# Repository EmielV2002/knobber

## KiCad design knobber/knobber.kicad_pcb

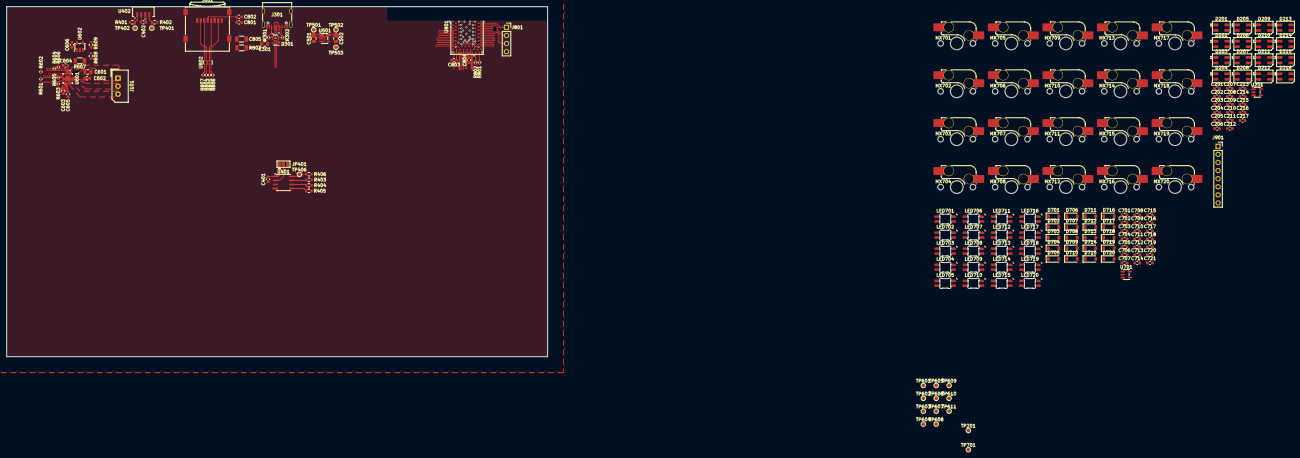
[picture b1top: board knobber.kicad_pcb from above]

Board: 4 copper layers, 189 parts (0 on the bottom side), 107 nets.

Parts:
C201, C202, C203, C204, C205, C206, C207, C208, C209, C210, C211, C212, C213, C214, C215, C216, C217, C401, C402, C701, C702, C703, C704, C705, C706, C707, C708, C709, C710, C711, C712, C713, C714, C715, C716, C717, C718, C719, C720, C721, C804: 0.1uF; C_0603_1608Metric
C301: 100nF; C_0805_2012Metric
C501, C502, C601: 10uF; C_0805_2012Metric
C602, C603, C604, C605, C606: 0.1nF; C_0603_1608Metric
C801, C802: 4.7uF; C_0603_1608Metric
C803: 10uF; C_0603_1608Metric
C805: 2.2uF; C_1206_3216Metric
D201, D202, D203, D204, D205, D206, D207, D208, D209, D210, D211, D212, D213, D214, D215, D216: SK6812MINI; LED_SK6812MINI_PLCC4_3.5x3.5mm_P1.75mm
D301: PRTR5V0U2X; SOT-143
D701, D702, D703, D704, D705, D706, D707, D708, D709, D710, D711, D712, D713, D714, D715, D716, D717, D718, D719, D720: 1N4148W; D_SOD-123
J101: BLDC; Molex_SPOX_5267-03A_1x03_P2.50mm_Vertical
J301: USB_C_Receptacle_USB2.0_16P; USB_C_Receptacle_G-Switch_GT-USB-7010ASV
J801: SWD; PinSocket_1x04_P2.54mm_Vertical
J802: Micro_SD_Card; microSD_HC_Wuerth_693072010801
J901: LCD; PinSocket_1x08_P2.54mm_Vertical
JP401: SolderJumper_3_Bridged12; SolderJumper-3_P1.3mm_Bridged12_Pad1.0x1.5mm
LED701, LED702, LED703, LED704, LED705, LED706, LED707, LED708, LED709, LED710, LED711, LED712, LED713, LED714, LED715, LED716, LED717, LED718, LED719, LED720: choc_SK6812MINI-E; LED_choc_6028R
MX701, MX702, MX703, MX704, MX705, MX706, MX707, MX708, MX709, MX710, MX711, MX712, MX713, MX714, MX715, MX716, MX717, MX718, MX719, MX720: MX_SW_HS; SW_MX_HS_CPG151101S11_1u
R301, R302: 5.1k; R_0402_1005Metric
R401, R402, R403, R404: 2.2k; R_0603_1608Metric
R405: 100k; R_0603_1608Metric
R406: 0; R_0603_1608Metric
R601, R602, R603, R604, R605, R606, R804, R805, R806, R807: 100k; R_0402_1005Metric
R607: 150m; R_1206_3216Metric
R608: 2k; R_0603_1608Metric
R609: 18k; R_0603_1608Metric
R801, R802: 27; R_0402_1005Metric
R803: 1M; R_1206_3216Metric
TP201, TP701: LED_DATA; TestPoint_Pad_D1.0mm
TP401: SDA; TestPoint_Pad_D1.0mm
TP402: SCL; TestPoint_Pad_D1.0mm
TP406: ENC__~{CS}; TestPoint_Pad_D1.0mm
TP501: 5V; TestPoint_Pad_D1.0mm
TP502: 3.3V; TestPoint_Pad_D1.0mm
TP503: GND; TestPoint_Pad_D1.0mm
TP601: MOT_UH; TestPoint_Pad_D1.0mm
TP602: MOT_UL; TestPoint_Pad_D1.0mm
TP603: MOT_VH; TestPoint_Pad_D1.0mm
TP604: MOT_VL; TestPoint_Pad_D1.0mm
TP605: MOT_WH; TestPoint_Pad_D1.0mm
TP606: MOT_WL; TestPoint_Pad_D1.0mm
TP607: Cur_sens; TestPoint_Pad_D1.0mm
TP608: MOT_DIAG; TestPoint_Pad_D1.0mm
TP609: MOT_U; TestPoint_Pad_D1.0mm
TP610: MOT_V; TestPoint_Pad_D1.0mm
TP611: MOT_W; TestPoint_Pad_D1.0mm
U201, U701: SN74LV1T34DBV; SOT-23-5
U401: MT6701CT; SO-8_3.9x4.9mm_P1.27mm
U402: VEML7700-TT
U501: AP2112K-3.3; SOT-23-5
U601: TMC6300-LA-T; QFN40P300X300X90-21N
U602: LMV321; SOT-23-5
U801: BMD-340-A-R; RIGADO_BMD-340-A-R
U802: ESD224DQA; Diodes_UDFN-10_1x2.5mm_P0.5mm

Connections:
3.3V: C402.1, C502.1, C603.1, C801.1, C802.1, C803.1, C804.1, J802.4 (VDD), J901.1, R401.2, R402.2, R403.2, R404.2, R804.2, R805.2, R806.2, R807.2, TP502.1, U402.2 (VDD), U501.5 (VOUT), U601.11 (VIO/~STDBY), U801.17 (VCC), U801.65 (VCCH)
5V: C201.1, C202.1, C203.1, C204.1, C205.1, C206.1, C207.1, C208.1, C209.1, C210.1, C211.1, C212.1, C213.1, C214.1, C215.1, C216.1, C217.1, C301.1, C401.1, C501.1, C601.1, C602.1, C604.1, C606.1, C701.1, C702.1, C703.1, C704.1, C705.1, C706.1, C707.1, C708.1, C709.1, C710.1, C711.1, C712.1, C713.1, C714.1, C715.1, C716.1, C717.1, C718.1, C719.1, C720.1, C721.1, D201.4 (VDD), D202.4 (VDD), D203.4 (VDD), D204.4 (VDD), D205.4 (VDD), D206.4 (VDD), D207.4 (VDD), D208.4 (VDD), D209.4 (VDD), D210.4 (VDD), D211.4 (VDD), D212.4 (VDD), D213.4 (VDD), D214.4 (VDD), D215.4 (VDD), D216.4 (VDD), D301.4 (VCC), J301.A4 (VBUS), J301.A9 (VBUS), J301.B4 (VBUS), J301.B9 (VBUS), JP401.1 (A), LED701.1 (VDD), LED702.1 (VDD), LED703.1 (VDD), LED704.1 (VDD), LED705.1 (VDD), LED706.1 (VDD), LED707.1 (VDD), LED708.1 (VDD), LED709.1 (VDD), LED710.1 (VDD), LED711.1 (VDD), LED712.1 (VDD), LED713.1 (VDD), LED714.1 (VDD), LED715.1 (VDD), LED716.1 (VDD), LED717.1 (VDD), LED718.1 (VDD), LED719.1 (VDD), LED720.1 (VDD), R406.2, TP501.1, U201.5 (VCC), U401.1 (VDD), U501.1 (VIN), U501.3 (EN), U601.2 (VCP), U601.18 (VS), U602.5 (V+), U701.5 (VCC), U801.66 (VBUS)
/MCU/SD_CLK: R805.1, U802.4
/MCU/SD_MISO: R806.1, U802.5
/MCU/SD_MOSI: R804.1, U802.2
/MCU/SD_~CS: R807.1, U802.1
/MCU/SW_CLK: J801.2, U801.43 (SWCLK)
/MCU/SW_DIO: J801.1, U801.44 (SWDIO)
/MCU/~RESET: J801.3, U801.39 (RESET)
/Motor driver/MOT_DIAG: TP608.1, U601.12 (DIAG)
/Motor driver/MOT_SENS: R609.1, U602.4
/Motor driver/MOT_U: J101.3, TP609.1, U601.15 (U)
/Motor driver/MOT_UH: R606.2, TP601.1, U601.3 (UH)
/Motor driver/MOT_UL: R605.2, TP602.1, U601.6 (UL)
/Motor driver/MOT_V: J101.2, TP610.1, U601.17 (V)
/Motor driver/MOT_VH: R604.2, TP603.1, U601.4 (VH)
/Motor driver/MOT_VL: R603.2, TP604.1, U601.10 (VL)
/Motor driver/MOT_W: J101.1, TP611.1, U601.1 (W)
/Motor driver/MOT_WH: R602.2, TP605.1, U601.5 (WH)
/Motor driver/MOT_WL: R601.2, TP606.1, U601.7 (WL)
/Sensors/ENC_CLK: R403.1, U401.7 (CLK)
/Sensors/ENC_MISO: R404.1, U401.6 (DO)
/Sensors/ENC__PUSH: R405.2, U401.5 (PUSH)
/Sensors/ENC__~CS: R406.1, TP406.1, U401.8 (~CS)
/Sensors/SCL: R401.1, TP402.1, U402.1 (SCL)
/Sensors/SDA: R402.1, TP401.1, U402.4 (SDA)
/Switches/COL_1: MX701.1, MX702.1, MX703.1, MX704.1, MX705.1
/Switches/COL_2: MX706.1, MX707.1, MX708.1, MX709.1, MX710.1
/Switches/COL_3: MX711.1, MX712.1, MX713.1, MX714.1, MX715.1
/Switches/COL_4: MX716.1, MX717.1, MX718.1, MX719.1, MX720.1
/Switches/ROW_1: D701.1 (K), D706.1 (K), D711.1 (K), D716.1 (K)
/Switches/ROW_2: D702.1 (K), D707.1 (K), D712.1 (K), D717.1 (K)
/Switches/ROW_3: D703.1 (K), D708.1 (K), D713.1 (K), D718.1 (K)
/Switches/ROW_4: D704.1 (K), D709.1 (K), D714.1 (K), D719.1 (K)
/Switches/ROW_5: D705.1 (K), D710.1 (K), D715.1 (K), D720.1 (K)
/USB/USB_CC1: J301.A5 (CC1), R302.2
/USB/USB_CC2: J301.B5 (CC2), R301.2
/USB/USB_D+: D301.3 (I/O2), J301.A6 (D+), J301.B6 (D+)
/USB/USB_D-: D301.2 (I/O1), J301.A7 (D-), J301.B7 (D-)
GND: C201.2, C202.2, C203.2, C204.2, C205.2, C206.2, C207.2, C208.2, C209.2, C210.2, C211.2, C212.2, C213.2, C214.2, C215.2, C216.2, C217.2, C301.2, C401.2, C402.2, C501.2, C502.2, C601.2, C602.2, C603.2, C604.2, C605.2, C606.2, C701.2, C702.2, C703.2, C704.2, C705.2, C706.2, C707.2, C708.2, C709.2, C710.2, C711.2, C712.2, C713.2, C714.2, C715.2, C716.2, C717.2, C718.2, C719.2, C720.2, C721.2, C801.2, C802.2, C803.2, C804.2, C805.2, D201.2 (VSS), D202.2 (VSS), D203.2 (VSS), D204.2 (VSS), D205.2 (VSS), D206.2 (VSS), D207.2 (VSS), D208.2 (VSS), D209.2 (VSS), D210.2 (VSS), D211.2 (VSS), D212.2 (VSS), D213.2 (VSS), D214.2 (VSS), D215.2 (VSS), D216.2 (VSS), D301.1 (GND), J301.A1 (GND), J301.A12 (GND), J301.B1 (GND), J301.B12 (GND), J301.S1 (SHIELD), J801.4, J802.6 (VSS), J901.2, JP401.3 (B), LED701.4 (VSS), LED702.4 (VSS), LED703.4 (VSS), LED704.4 (VSS), LED705.4 (VSS), LED706.4 (VSS), LED707.4 (VSS), LED708.4 (VSS), LED709.4 (VSS), LED710.4 (VSS), LED711.4 (VSS), LED712.4 (VSS), LED713.4 (VSS), LED714.4 (VSS), LED715.4 (VSS), LED716.4 (VSS), LED717.4 (VSS), LED718.4 (VSS), LED719.4 (VSS), LED720.4 (VSS), R301.1, R302.1, R405.1, R601.1, R602.1, R603.1, R604.1, R605.1, R606.1, R607.1, R608.1, R803.2, TP503.1, U201.3 (GND), U401.4 (GND), U402.3 (GND), U501.2 (GND), U601.8 (GND), U601.9 (GND), U601.14 (GND), U601.21 (EXP), U602.2 (V-), U701.3 (GND), U801.1 (GND), U801.2 (GND), U801.3 (GND), U801.4 (GND), U801.5 (GND), U801.16 (GND), U801.18 (GND), U801.29 (GND), U801.30 (GND), U801.45 (GND), U801.46 (GND), U801.47 (GND), U801.55 (GND), U802.3 (VSS), U802.8 (VSS)
unnamed: D201.3 (DIN), TP201.1, U201.4 (Y)
unnamed: D201.1 (DOUT), D203.3 (DIN)
unnamed: D202.3 (DIN), D215.1 (DOUT)
unnamed: D202.1 (DOUT), D204.3 (DIN)
unnamed: D203.1 (DOUT), D205.3 (DIN)
unnamed: D204.1 (DOUT), D206.3 (DIN)
unnamed: D205.1 (DOUT), D207.3 (DIN)
unnamed: D206.1 (DOUT), D208.3 (DIN)
unnamed: D207.1 (DOUT), D209.3 (DIN)
unnamed: D208.1 (DOUT), D210.3 (DIN)
unnamed: D209.1 (DOUT), D211.3 (DIN)
unnamed: D210.1 (DOUT), D212.3 (DIN)
unnamed: D211.1 (DOUT), D213.3 (DIN)
unnamed: D212.1 (DOUT), D214.3 (DIN)
unnamed: D213.1 (DOUT), D215.3 (DIN)
unnamed: D214.1 (DOUT), D216.3 (DIN)
unnamed: D701.2 (A), MX701.2
unnamed: D702.2 (A), MX702.2
unnamed: D703.2 (A), MX703.2
unnamed: D704.2 (A), MX704.2
unnamed: D705.2 (A), MX705.2
unnamed: D706.2 (A), MX706.2
unnamed: D707.2 (A), MX707.2
unnamed: D708.2 (A), MX708.2
unnamed: D709.2 (A), MX709.2
unnamed: D710.2 (A), MX710.2
unnamed: D711.2 (A), MX711.2
unnamed: D712.2 (A), MX712.2
unnamed: D713.2 (A), MX713.2
unnamed: D714.2 (A), MX714.2
unnamed: D715.2 (A), MX715.2
unnamed: D716.2 (A), MX716.2
unnamed: D717.2 (A), MX717.2
unnamed: D718.2 (A), MX718.2
unnamed: D719.2 (A), MX719.2
unnamed: D720.2 (A), MX720.2
unnamed: J802.5 (CLK), U802.7
unnamed: J802.3 (CMD), U802.9
unnamed: J802.7 (DAT0), U802.6
unnamed: J802.2 (DAT3/CD), U802.10
unnamed: C805.1, J802.9 (SHIELD), R803.1
unnamed: JP401.2 (C), U401.2 (MODE)
unnamed: LED701.3 (DIN), TP701.1, U701.4 (Y)
unnamed: LED701.2 (DOUT), LED706.3 (DIN)
unnamed: LED702.3 (DIN), LED716.2 (DOUT)
unnamed: LED702.2 (DOUT), LED707.3 (DIN)
unnamed: LED703.3 (DIN), LED717.2 (DOUT)
unnamed: LED703.2 (DOUT), LED708.3 (DIN)
unnamed: LED704.3 (DIN), LED718.2 (DOUT)
unnamed: LED704.2 (DOUT), LED709.3 (DIN)
unnamed: LED705.3 (DIN), LED719.2 (DOUT)
unnamed: LED705.2 (DOUT), LED710.3 (DIN)
unnamed: LED706.2 (DOUT), LED711.3 (DIN)
unnamed: LED707.2 (DOUT), LED712.3 (DIN)
unnamed: LED708.2 (DOUT), LED713.3 (DIN)
unnamed: LED709.2 (DOUT), LED714.3 (DIN)
unnamed: LED710.2 (DOUT), LED715.3 (DIN)
unnamed: LED711.2 (DOUT), LED716.3 (DIN)
unnamed: LED712.2 (DOUT), LED717.3 (DIN)
unnamed: LED713.2 (DOUT), LED718.3 (DIN)
unnamed: LED714.2 (DOUT), LED719.3 (DIN)
unnamed: LED715.2 (DOUT), LED720.3 (DIN)
unnamed: C605.1, U601.13 (1.8VOUT)
unnamed: R607.2, TP607.1, U601.16 (BRUV), U601.20 (BRW), U602.1 (+)
unnamed: R608.2, R609.2, U602.3 (-)
unnamed: R801.2, U801.68 (USB-D+)
unnamed: R802.2, U801.67 (USB-D-)

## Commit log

2026-03-16 Updated schematic & PCB
